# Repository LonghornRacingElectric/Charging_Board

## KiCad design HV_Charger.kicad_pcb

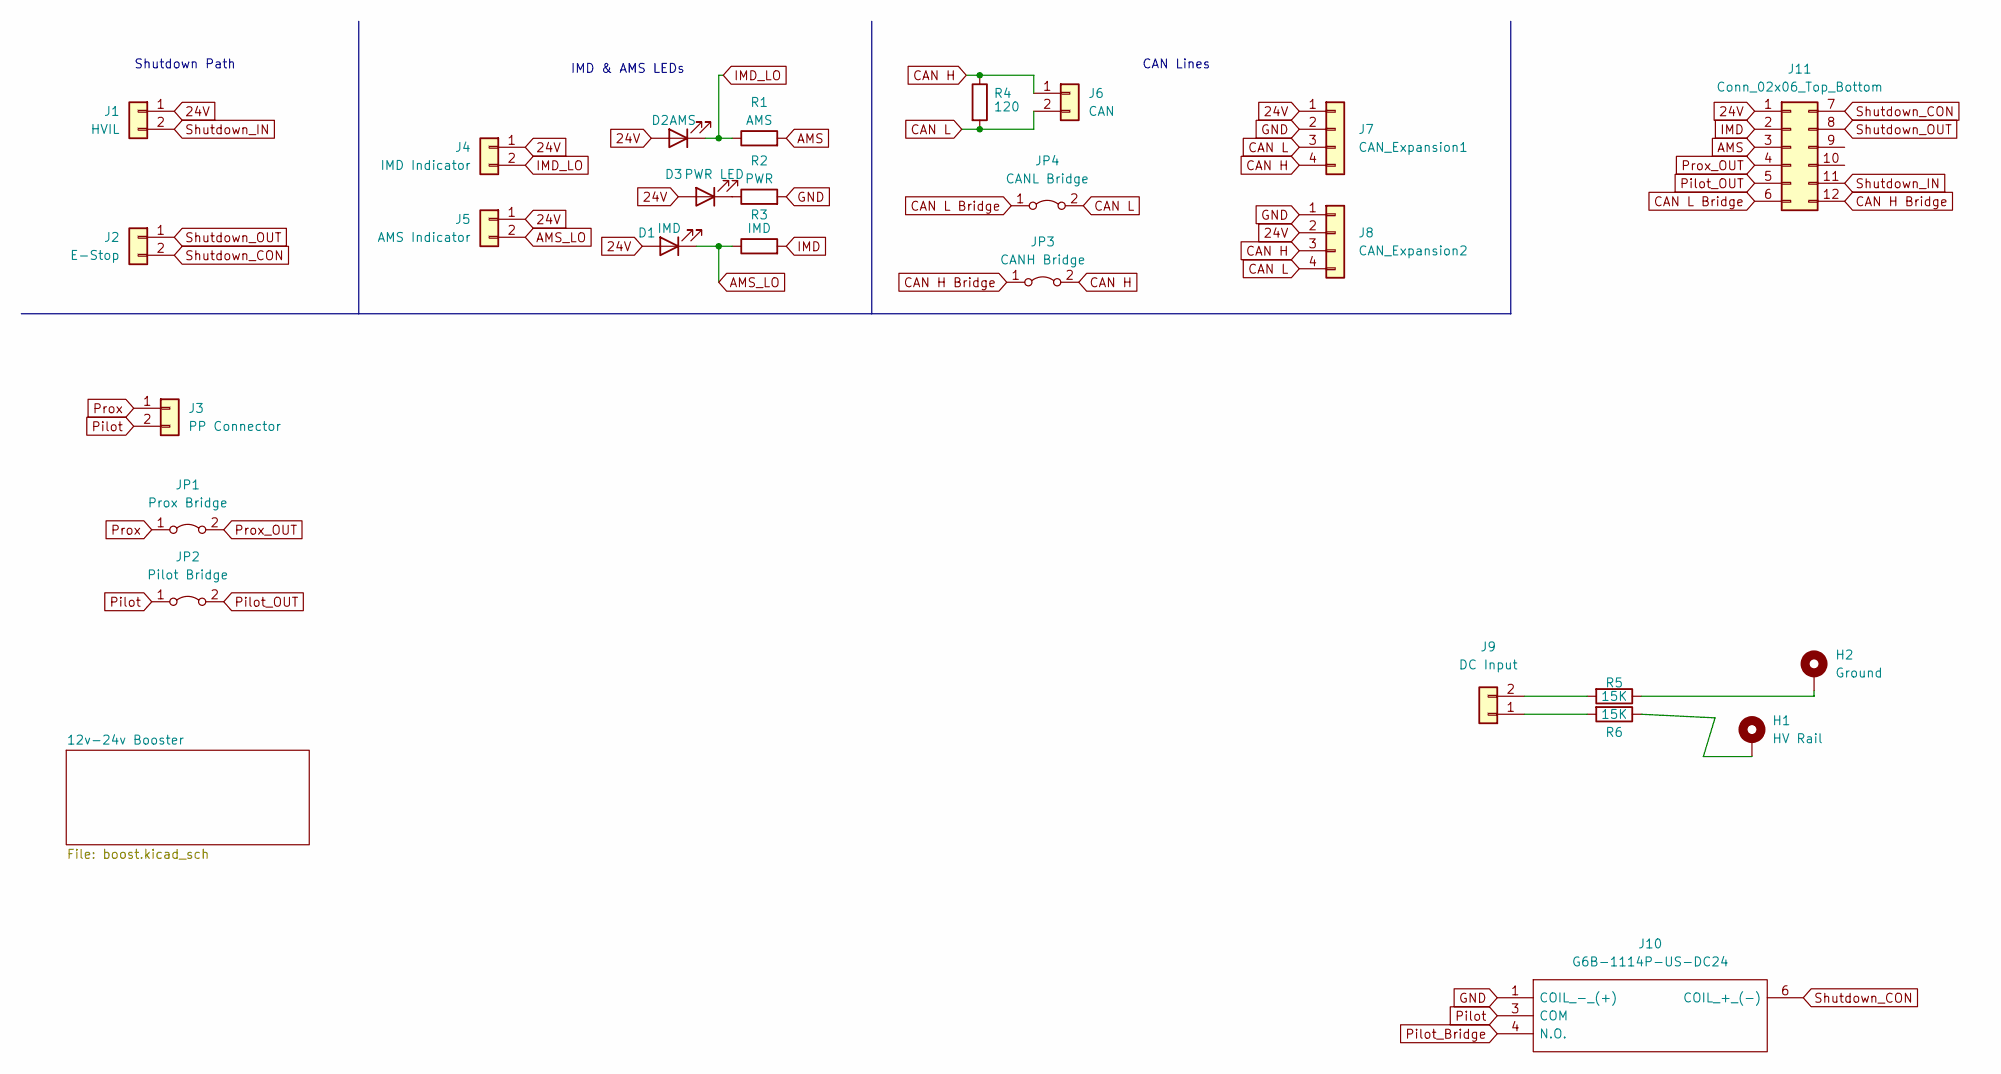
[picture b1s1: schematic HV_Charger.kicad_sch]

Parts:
D1: IMD; LED_0603_1608Metric
D2: AMS; LED_0603_1608Metric
D3: PWR LED; LED_0603_1608Metric
H1: HV Rail; Banana_Jack
H2: Ground; Banana_Jack
J1: HVIL; Molex_Micro-Fit_3.0_43045-0212_2x01_P3.00mm_Vertical
J2: E-Stop; Molex_Micro-Fit_3.0_43045-0212_2x01_P3.00mm_Vertical
J3: PP Connector; Molex_Micro-Fit_3.0_43045-0212_2x01_P3.00mm_Vertical
J4: IMD Indicator; Molex_Micro-Fit_3.0_43045-0212_2x01_P3.00mm_Vertical
J5: AMS Indicator; Molex_Micro-Fit_3.0_43045-0212_2x01_P3.00mm_Vertical
J6: CAN; Molex_Micro-Fit_3.0_43045-0212_2x01_P3.00mm_Vertical
J7: CAN_Expansion1; Molex_Micro-Fit_3.0_43045-0412_2x02_P3.00mm_Vertical
J8: CAN_Expansion2; Molex_Micro-Fit_3.0_43045-0412_2x02_P3.00mm_Vertical
J9: DC Input; Molex_Micro-Fit_3.0_43045-0212_2x01_P3.00mm_Vertical
J10: G6B-1114P-US-DC24; G6B1114PUSDC24; Mouser Part Number 653-G6B-1114P-DC24
J11: Conn_02x06_Top_Bottom; Molex_Micro-Fit_3.0_43045-1212_2x06_P3.00mm_Vertical
JP1: Prox Bridge; SolderJumper-2_P1.3mm_Open_Pad1.0x1.5mm
JP2: Pilot Bridge; SolderJumper-2_P1.3mm_Open_Pad1.0x1.5mm
JP3: CANH Bridge; SolderJumper-2_P1.3mm_Open_Pad1.0x1.5mm
JP4: CANL Bridge; SolderJumper-2_P1.3mm_Open_Pad1.0x1.5mm
R1: AMS; R_0603_1608Metric
R2: PWR; R_0603_1608Metric
R3: IMD; R_0603_1608Metric
R4: 120; R_0603_1608Metric
R5, R6: 15K; RESC11050X120N

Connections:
24V: D1.2 (A), D2.2 (A), D3.2 (A), J1.1, J4.1, J5.1, J7.1, J8.2, J11.1; also elsewhere on the board
AMS: J11.3, R1.2
AMS_LO: D1.1 (K), J5.2, R3.1
CAN H: J6.1, J7.4, J8.3, JP3.2 (B), R4.1
CAN H Bridge: J11.12, JP3.1 (A)
CAN L: J6.2, J7.3, J8.4, JP4.2 (B), R4.2
CAN L Bridge: J11.6, JP4.1 (A)
GND: J7.2, J8.1, J10.1 (COIL_-_(+)), R2.2; also elsewhere on the board
IMD: J11.2, R3.2
IMD_LO: D2.1 (K), J4.2, R1.1
unnamed: D3.1 (K), R2.1
unnamed: H1.1, R6.1
unnamed: H2.1, R5.1
unnamed: J9.1, R6.2
unnamed: J9.2, R5.2
Pilot: J3.2, J10.3 (COM), JP2.1 (A)
Pilot_OUT: J11.5, JP2.2 (B)
Prox: J3.1, JP1.1 (A)
Prox_OUT: J11.4, JP1.2 (B)
Shutdown_CON: J2.2, J10.6 (COIL_+_(-)), J11.7
Shutdown_IN: J1.2, J11.11
Shutdown_OUT: J2.1, J11.8

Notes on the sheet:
CAN Lines
IMD & AMS LEDs
Shutdown Path

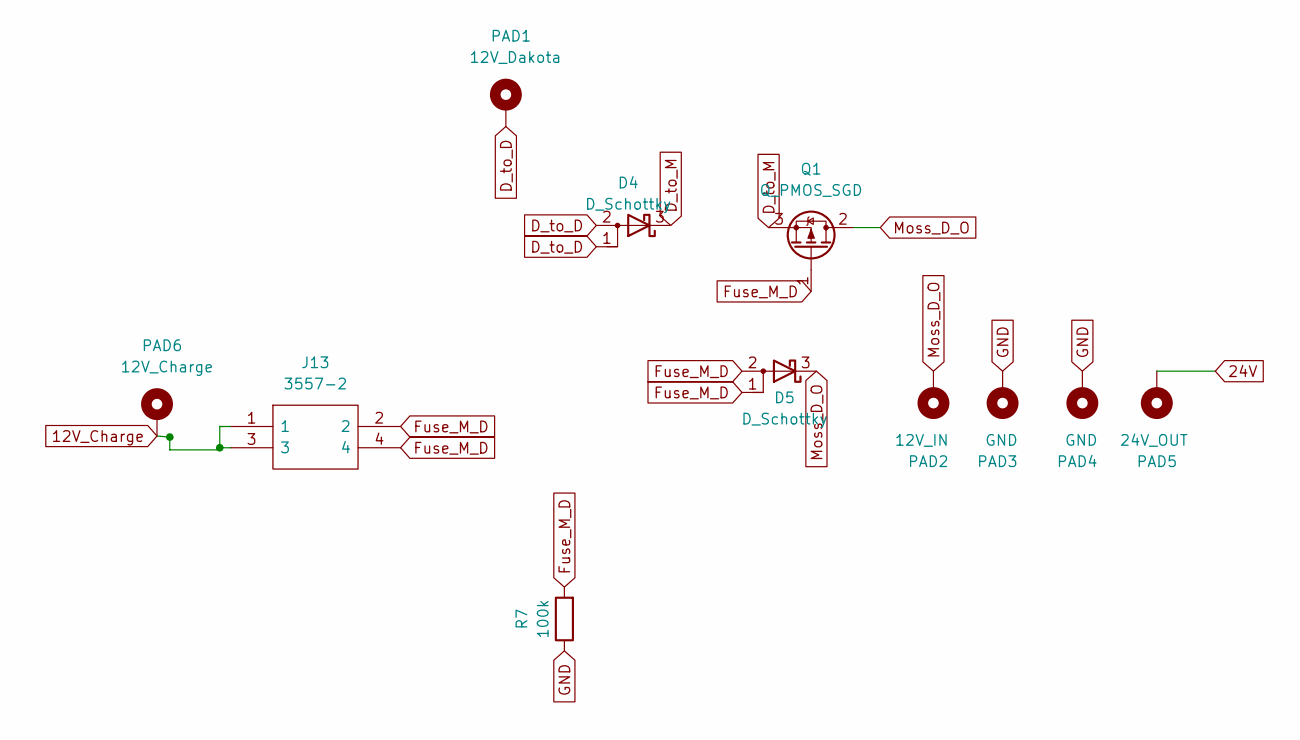
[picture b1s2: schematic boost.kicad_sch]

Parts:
D4, D5: D_Schottky; RBQ10RSM10BTL1
J13: 3557-2; Manufacturer_Part_Number 3557-2; Mouser Part Number 534-3557-2
PAD1: 12V_Dakota; TestPoint_Pad_4.0x4.0mm
PAD2: 12V_IN; TestPoint_Pad_4.0x4.0mm
PAD3, PAD4: GND; TestPoint_Pad_4.0x4.0mm
PAD5: 24V_OUT; TestPoint_Pad_4.0x4.0mm
PAD6: 12V_Charge; TestPoint_Pad_4.0x4.0mm
Q1: Q_PMOS_SGD; BTS3035TFATMA1
R7: 100k; R_0603_1608Metric

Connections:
12V_Charge: J13.1, J13.3, PAD6.1
24V: PAD5.1; also elsewhere on the board
D_to_D: D4.1 (A), D4.2 (A), PAD1.1
D_to_M: D4.3 (K), Q1.3 (S)
Fuse_M_D: D5.1 (A), D5.2 (A), J13.2, J13.4, Q1.1 (G), R7.2
GND: PAD3.1, PAD4.1, R7.1; also elsewhere on the board
Moss_D_O: D5.3 (K), PAD2.1, Q1.2 (D)

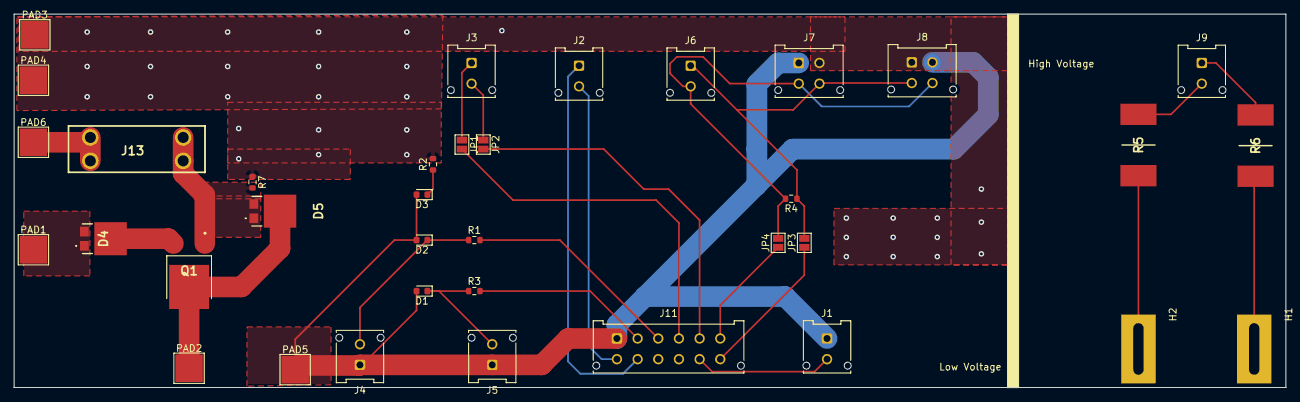
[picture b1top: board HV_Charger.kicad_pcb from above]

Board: 2 copper layers, 184.6 x 54.2 mm, 36 parts (0 on the bottom side), 27 nets.

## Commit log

2023-02-12 First Comms
2023-02-12 Foot added
2023-02-13 footprint added for pmos
2023-02-19 Fixed Rylan issues, pls switch diodes on pmos
2023-02-19 Fixed Rylan issues, pls change diode direction on pmos, Also Arjun pushed wrong format and messed up my end >:(
2023-02-19 Finished Schematic?
2023-03-05 did basic layout
2023-03-05 more stuff done
2023-03-05 Added more footprints and did layout, banana jack left to do:
2023-03-05 Done
2023-03-05 Made corrections
